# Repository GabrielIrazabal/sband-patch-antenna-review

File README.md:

# S-band patch antenna for a 1U CubeSat

A right-hand circularly polarized patch antenna for a 2.4 GHz downlink. This repo holds the two cut-corner designs, the three size versions planned for the first order, and the dual-feed designs as a supplement. Each one has its KiCad board, its Gerbers and its Ansys HFSS results.

**Status: simulation only. Nothing has been built or measured yet.**

Author: Gabriel Irazabal

## Contents

1. [Requirements](#1-requirements)
2. [How everything was simulated](#2-how-everything-was-simulated)
3. [Cut corner, 1.5 mm](#3-cut-corner-15-mm)
4. [Cut corner, 3 mm (stacked)](#4-cut-corner-3-mm-stacked)
5. [Manufacturing tolerance and the proposed first order](#5-manufacturing-tolerance-and-the-proposed-first-order)
6. [Supplementary: dual feed](#6-supplementary-dual-feed)
7. [How to check this work](#7-how-to-check-this-work)
8. [What has not been verified](#8-what-has-not-been-verified)

## 1. Requirements

| Requirement | Target |
| --- | --- |
| Frequency | 2.4 GHz band |
| Signal bandwidth | 20 MHz or less |
| Gain | 6.5 dBi or more (ideally 7 or more) |
| Beamwidth | half-power beamwidth 60° or wider |
| Polarization | right-hand circular |
| Impedance | 50 Ω |
| Power handling | 3 W or more |
| Environment | −40 to +85 °C |
| Direction | transmit and receive |
| Match bandwidth | return loss 10 dB or more across the full 20 MHz channel |
| Connector | SMA |

The designs are centred on 2.425 GHz, with the channel taken as 2.415 to 2.435 GHz.

## 2. How everything was simulated

| Item | Value |
| --- | --- |
| Tool | Ansys HFSS (Electronics Desktop Student 2025 R2) |
| Board material | JLCPCB PTFE, ZYF255DA: Dk 2.55, loss tangent 0.0018 |
| Board | 60 × 60 mm, 1.524 mm thick, 35 µm copper |
| Mounting | board flat on a 100 × 100 mm metal face, which stands in for the satellite panel |
| Feed | 0.5 mm pin through the board, 50 Ω lumped port |
| Mesh | refined to about 40,000 tetrahedra |
| Far field | RHCP and LHCP gain and axial ratio straight ahead, and gain against angle at 2.425 GHz |

In the plots, match is shown as S11. S11 is return loss with a minus sign, so "S11 of −10 dB or lower" is the same as "return loss of 10 dB or more".

## 3. Cut corner, 1.5 mm

One board. A square patch with two opposite corners clipped, fed by one pin. The clipped corners are what make it circularly polarized.

Folder: [`1_cut_corner_1.5mm`](1_cut_corner_1.5mm)

| Front | Back |
| --- | --- |
|  |  |

### Dimensions

| Item | Value |
| --- | --- |
| Board | 60 × 60 × 1.524 mm |
| Patch | 37.52 mm square, centred |
| Clipped corners | top-left and bottom-right (seen from the front), 3.50 mm along each edge |
| Feed | plated via, 0.5 mm hole, 7.00 mm to the right of the patch centre |
| Ground | whole back of the board |
| Connector | surface-mount SMA on the back (Würth 60312102114405), centre pad on the feed via |
| Solder mask | none on the front |
| Mounting holes | four M3, 4 mm in from each edge |

### Ansys HFSS results

| Requirement | Result | Meets it |
| --- | --- | --- |
| Frequency: 2.4 GHz band | best polarization at 2.425 GHz | yes |
| Signal bandwidth 20 MHz | return loss above 10 dB from 2.400 to 2.466 GHz (66 MHz) | yes |
| Gain 6.5 dBi or more | 7.08 to 7.24 dBic across the channel | yes |
| Beamwidth 60° or wider | 72° and 73° in the two cuts | yes |
| Right-hand circular | RHCP is 32 dB above LHCP at 2.425 GHz | yes |
| 50 Ω | best match −31.8 dB at 2.4455 GHz | yes |
| Return loss 10 dB over the channel | worst point in the channel 15.5 dB | yes |

Other figures: directivity 7.97 dBi, radiation efficiency 87 %.

**The known weak point is polarization at the channel edges.** The axial ratio is 0.43 dB at the centre and 4.14 dB at the edges, and it stays under 3 dB over 16 MHz. An axial ratio of 4.14 dB costs about 0.23 dB of signal to a perfectly circular ground antenna. The gain figures above already include that.

| Match | Axial ratio |
| --- | --- |
|  |  |

| Gain | Pattern |
| --- | --- |
|  |  |

### Files

| What | Where |
| --- | --- |
| KiCad project | [`1_cut_corner_1.5mm/kicad`](1_cut_corner_1.5mm/kicad) |
| Gerbers for JLCPCB | [`1_cut_corner_1.5mm/gerbers/Cutcorner_antenna.zip`](1_cut_corner_1.5mm/gerbers/Cutcorner_antenna.zip) |
| Ansys project and raw results | [`1_cut_corner_1.5mm/ansys`](1_cut_corner_1.5mm/ansys) |

## 4. Cut corner, 3 mm (stacked)

Folder: [`2_cut_corner_3mm_stacked`](2_cut_corner_3mm_stacked)

| TOP board, front | BOTTOM board, back |
| --- | --- |
|  |  |

### Dimensions

| Item | Value |
| --- | --- |
| Boards | two, each 60 × 60 × 1.524 mm, giving 3.05 mm of PTFE between patch and ground |
| Patch (on the TOP board) | 37.10 mm square, centred |
| Clipped corners | top-left and bottom-right, 5.55 mm along each edge |
| Feed | 0.6 mm hole through both boards, 8.00 mm to the right of the patch centre and 2.18 mm up |
| Ground (on the BOTTOM board) | whole back |
| Connector | the same SMA, on the back of the BOTTOM board |
| Copper on the two glued faces | none |

The feed sits 2.18 mm off the centre line on purpose. A pin through 3 mm of board adds inductance, and the sideways offset cancels it.

### How it goes together

1. Glue the TOP board onto the BOTTOM board with a thin, even layer of adhesive, using the four M3 holes to line them up. There must be no air between them.
2. Solder the SMA to the back of the BOTTOM board.
3. Pass a 0.5 mm wire through the feed hole in both boards. Solder it to the SMA centre pad at the back and to the patch at the front, and trim it flush.

The wire is needed because the plating inside each board's hole does not connect across the glue layer.

### Ansys HFSS results

| Requirement | Result | Meets it |
| --- | --- | --- |
| Frequency: 2.4 GHz band | best polarization at 2.425 GHz | yes |
| Signal bandwidth 20 MHz | return loss above 10 dB from 2.356 to 2.487 GHz (131 MHz) | yes |
| Gain 6.5 dBi or more | 7.61 to 7.67 dBic across the channel | yes |
| Beamwidth 60° or wider | 73° in both cuts | yes |
| Right-hand circular | RHCP is 33 dB above LHCP at 2.425 GHz | yes |
| 50 Ω | best match −38.6 dB at 2.394 GHz | yes |
| Return loss 10 dB over the channel | worst point in the channel 19.1 dB | yes |

Other figures: directivity 7.96 dBi, radiation efficiency 95 %. The axial ratio is 0.38 dB at the centre and 2.17 dB at the channel edges, and stays under 3 dB over 32 MHz.

| Match | Axial ratio |
| --- | --- |
|  |  |

| Gain | Pattern |
| --- | --- |
|  |  |

### Thin against thick

| | Cut corner, 1.5 mm | Cut corner, 3 mm |
| --- | --- | --- |
| RHCP gain in the channel | 7.08 to 7.24 dBic | 7.61 to 7.67 dBic |
| Worst return loss in the channel | 15.5 dB | 19.1 dB |
| Match bandwidth | 66 MHz | 131 MHz |
| Axial ratio at the channel edges | 4.14 dB | 2.17 dB |
| Bandwidth with axial ratio under 3 dB | 16 MHz | 32 MHz |
| Efficiency | 87 % | 95 % |
| Build | one board | two boards, a glue joint and a feed wire |

**The weak point of the 3 mm version is the glue joint.** In simulation, a 0.05 mm film of air between the boards raises the worst axial ratio in the channel from 2.2 to 6.5 dB.

### Files

| What | Where |
| --- | --- |
| KiCad projects, TOP and BOTTOM | [`2_cut_corner_3mm_stacked/kicad`](2_cut_corner_3mm_stacked/kicad) |
| Gerbers for JLCPCB | [`2_cut_corner_3mm_stacked/gerbers`](2_cut_corner_3mm_stacked/gerbers) |
| Ansys project and raw results | [`2_cut_corner_3mm_stacked/ansys`](2_cut_corner_3mm_stacked/ansys) |

## 5. Manufacturing tolerance and the proposed first order

**Proposal: order the 1.5 mm cut corner in three sizes (the design size, 0.3 mm smaller and 0.3 mm larger), measure all of them, and fly the one closest to 2.425 GHz.** This section explains the problem that makes this necessary.

Folder: [`3_three_sizes`](3_three_sizes) (the design size is in [`1_cut_corner_1.5mm`](1_cut_corner_1.5mm))

### The problem

A patch antenna's frequency is set by the patch size and the board it sits on, and a factory cannot make either exactly as drawn. For JLCPCB's PTFE (ZYF255DA, 1.524 mm) the expected errors are:

| What varies | By how much | Frequency shift |
| --- | --- | --- |
| Dk of the PTFE | 2.55 ± 0.04 (laminate datasheet) | about ±18 MHz |
| Board thickness | ±10 % (JLCPCB) | about ±9 MHz (+10 thin, −7.5 thick) |
| Etched patch size | about ±0.05 mm | about ±3 MHz |
| **All together** | | **about ±20 to ±23 MHz** |

The total is the root-sum-square of the three, since they are independent. That is as wide as the 20 MHz channel itself. The Dk figure comes from HFSS runs of this board with Dk set to 2.52 and 2.58, and the patch-size figure from the three sizes below. The thickness figure is from a separate check in a second solver (openEMS) at 1.37 and 1.68 mm.

Sources: [ZYF255DA datasheet (hosted by JLCPCB)](https://rs.jlcpcb.com/static/file/ptfe-teflon-datasheet.pdf), [JLCPCB PCB capabilities](https://jlcpcb.com/capabilities/pcb-capabilities).

### What an off-frequency board does

The table reads the design-size HFSS curves as if the whole antenna had moved up or down in frequency, and reports the worst point inside the 2.415 to 2.435 GHz channel.

| Board lands | Worst axial ratio | Lowest RHCP gain | Worst return loss | Meets gain 6.5 and return loss 10? |
| --- | --- | --- | --- | --- |
| On target | 4.1 dB | 7.08 dBic | 15.5 dB | yes |
| 10 MHz high | 7.0 dB | 6.47 dBic | 12.3 dB | gain just under |
| 10 MHz low | 7.6 dB | 6.72 dBic | 15.5 dB | yes |
| 20 MHz high | 10.4 dB | 5.49 dBic | 8.2 dB | no |
| 20 MHz low | 10.9 dB | 6.17 dBic | 16.6 dB | gain no |

The gain column is realized gain, so it already includes the polarization and mismatch losses. Polarization degrades first: the cut corner keeps its axial ratio under 3 dB over only 16 MHz. The 20 MHz rows use the end of the HFSS sweep (2.395 GHz), so they are approximate.

### Temperature

The Dk of the PTFE changes by −115 ppm/°C (datasheet), and the copper grows by about 15.5 ppm/°C, which partly cancels it. In HFSS the 1.5 mm cut corner moves −5 MHz at −40 °C and +6 MHz at +85 °C, and still meets the requirements at both:

| 1.5 mm cut corner | Best match moves | Lowest gain | Worst return loss | Worst axial ratio |
| --- | --- | --- | --- | --- |
| −40 °C | −5.0 MHz | 6.87 dBic | 15.1 dB | 6.1 dB |
| 20 °C (nominal) | 0 | 7.08 dBic | 15.5 dB | 4.1 dB |
| +85 °C | +6.0 MHz | 6.73 dBic | 13.3 dB | 5.9 dB |

This drift comes on top of the manufacturing error, and it affects every board the same way, so choosing a size cannot remove it. It is about ±6 MHz, so a board that lands within about ±10 MHz at room temperature still has some margin. The 1.5 mm dual feed fails this same check (section 6).

### Options considered

| Option | Frequency error | Notes |
| --- | --- | --- |
| **JLCPCB PTFE, three sizes** (proposed) | about ±20 MHz, covered by the three sizes | $175 per size (5 boards), about $525 for all three. Designed and simulated. |
| JLCPCB PTFE, one size | about ±20 MHz | A board 20 MHz off misses the gain requirement (table above). |
| Rogers RO4350B or RO4003C | about ±17 MHz | Dk 3.48 / 3.38 ± 0.05. Tolerance barely better, and RO4350B simulated at 5.6 to 6.3 dBic, below the 6.5 requirement. |
| Rogers RT/duroid 5880 (or Taconic TLY-5) | about ±12 MHz (estimate) | Dk 2.20 ± 0.02, 1.575 mm ± 0.076 mm. Roughly halves the error. Not designed or simulated yet (patch about 40 mm). Not offered by JLCPCB. PCBWay lists it, but only as a manual quote for non-stocked material. |

Sources: [RT/duroid 5880 datasheet (Rogers)](https://www.rogerscorp.com/-/media/project/rogerscorp/documents/advanced-electronics-solutions/english/data-sheets/rt-duroid-5870---5880-data-sheet.pdf), [PCBWay material list](https://www.pcbway.com/pcb_prototype/PCB_material_classification.html).

### What changed between the three sizes

Only the side of the patch. The corner cuts, the feed position, the board and everything else are identical. A smaller patch resonates higher and a larger one lower.

| Version | Patch side | Best polarization at | Best match at | Shift from the design size |
| --- | --- | --- | --- | --- |
| Smaller | 37.22 mm | 2.4425 GHz | 2.4630 GHz | +17.5 MHz |
| Design size | 37.52 mm | 2.4250 GHz | 2.4455 GHz | 0 |
| Larger | 37.82 mm | 2.4050 GHz | 2.4280 GHz | −17.5 to −20 MHz |

So the three are about 19 MHz apart, or about 62 MHz per millimetre of patch side. The far-field sweep is in 2.5 MHz steps, which is why the two shifts are not exactly equal.

### How they are used

All three are made in the same batch, so they share the same material and thickness errors. Each is measured on a network analyzer, and the one that lands closest to 2.425 GHz is the one that flies. If the factory makes everything about 20 MHz low, that is the smaller one; if about 20 MHz high, the larger one.

Because the sizes are 19 MHz apart, the best of the three should land within about ±10 MHz of 2.425 GHz for any factory error up to about ±30 MHz. From the table above, a board 10 MHz off still gives about 6.5 to 6.7 dBic. A spare from the same batch is the backup for the flight board.

### Files

| What | Where |
| --- | --- |
| KiCad projects | [`3_three_sizes/kicad`](3_three_sizes/kicad) |
| Gerbers for JLCPCB | [`3_three_sizes/gerbers`](3_three_sizes/gerbers) |
| Ansys projects and raw results | [`3_three_sizes/ansys`](3_three_sizes/ansys) |

## 6. Supplementary: dual feed

The other way to make a patch circularly polarized. A plain square patch gets two feed pins, one on each axis, driven a quarter cycle apart by an external 90° coupler. It is not the plan for this satellite, because the radio board has one S-band connector and no coupler, but it was designed and simulated as the alternative.

Folder: [`supplementary_dual_feed`](supplementary_dual_feed)

| Front | Back |
| --- | --- |
|  |  |

### Dimensions

| | Dual feed, 1.5 mm | Dual feed, 3 mm (stacked) |
| --- | --- | --- |
| Patch | 37.28 mm square | 36.39 mm square |
| Clipped corners | none | none |
| Feeds | 5.80 mm right of centre (J1) and 5.80 mm above centre (J2) | 6.70 mm right of centre (J1) and 6.70 mm above centre (J2) |
| Connectors | two SMAs | two SMAs |
| Build | one board | TOP and BOTTOM boards glued, as in section 4 |

It is right-hand circular when J2 lags J1 by 90°.

### Ansys HFSS results

| | Dual feed, 1.5 mm | Dual feed, 3 mm |
| --- | --- | --- |
| RHCP gain in the channel, at the patch | 7.16 to 7.36 dBic | 7.67 to 7.72 dBic |
| RHCP gain after a typical coupler | 6.75 to 6.96 dBic | 7.26 to 7.32 dBic |
| Worst return loss in the channel | 13.6 dB | 16.4 dB |
| Match bandwidth | 32 MHz | 63 MHz |
| Axial ratio, perfect coupler | 0.11 dB | 0.28 dB |
| Axial ratio, typical coupler | 0.79 dB | 0.94 dB |
| Isolation between the two feeds | 46 dB | 36 dB |
| Half-power beamwidth | 72° and 73° | 73° |
| Radiation efficiency | 87 % | 95 % |

"Typical coupler" means one that is off by 0.5 dB and 3° and loses 0.4 dB. The coupler itself was not modelled.

### Temperature and manufacturing checks: the 1.5 mm dual feed does not hold

Both dual feeds were rerun in HFSS (24 and 25 November) with the effects that real boards add. For temperature, the Dk was scaled by the datasheet's −115 ppm/°C and the copper dimensions by 15.5 ppm/°C, from 20 °C. The whole board was held at one temperature.

| Dual feed, 1.5 mm | Best match moves | Lowest gain (after coupler) | Worst return loss | Requirements |
| --- | --- | --- | --- | --- |
| Nominal | 0 | 6.75 dBic | 13.6 dB | pass |
| Finest mesh | +1.0 MHz | 6.70 dBic | 12.8 dB | pass |
| With the SMA connector | −4.0 MHz | 6.58 dBic | 11.0 dB | pass |
| With solder mask on the top | −8.5 MHz | 6.38 dBic | 9.1 dB | **fail** |
| −40 °C | −6.5 MHz | 6.50 dBic | 9.9 dB | **fail** |
| +85 °C | +6.5 MHz | 6.43 dBic | 9.8 dB | **fail** |

**Its match window is only 32 MHz wide, and a ±6 MHz temperature drift is enough to take the channel edge below 10 dB return loss.** It fails the match requirement at both temperature extremes and the gain requirement at +85 °C. The manufacturing tolerances in section 5 (about ±20 MHz) are three times larger than that drift, so this design has no margin left for them. The second solver (openEMS) already put it at 6.49 dBic at nominal.

| Dual feed, 3 mm | Best match moves | Lowest gain (after coupler) | Worst return loss | Requirements |
| --- | --- | --- | --- | --- |
| Nominal | 0 | 7.26 dBic | 16.4 dB | pass |
| −40 °C / +85 °C | −5.5 / +6.0 MHz | 7.18 / 7.21 dBic | 13.9 / 15.8 dB | pass |
| SMA and glue-joint layer, as drawn | −15.0 MHz | 6.99 dBic | 10.8 dB | pass, narrowly |
| The same plus solder mask on the top | −24.0 MHz | 6.83 dBic | 9.0 dB | **fail** |

The 3 mm dual feed survives temperature, but the SMA, the glue joint and any top mask all pull it lower in frequency, and the shifts add up. As drawn it keeps only 0.8 dB of return loss in hand, before manufacturing tolerance is counted.

For comparison, both cut corners pass all of these checks on gain and return loss (section 5 has the 1.5 mm temperature figures).

### Compared with the cut corner

| | Cut corner | Dual feed |
| --- | --- | --- |
| Polarization | good at the centre, weaker at the channel edges | good across the whole channel |
| Extra parts | none | a 90° coupler, a load, a second cable and a second connector |
| Gain | higher | about 0.3 to 0.4 dB lower, because of the coupler |
| Match bandwidth | wider | half as wide |
| −40 °C and +85 °C (HFSS) | holds at 1.5 mm and 3 mm | fails at 1.5 mm, holds at 3 mm |

### Files

| What | 1.5 mm | 3 mm |
| --- | --- | --- |
| KiCad | [`kicad`](supplementary_dual_feed/1.5mm/kicad) | [`kicad`](supplementary_dual_feed/3mm_stacked/kicad) |
| Gerbers | [`gerbers`](supplementary_dual_feed/1.5mm/gerbers) | [`gerbers`](supplementary_dual_feed/3mm_stacked/gerbers) |
| Ansys project and raw results | [`ansys`](supplementary_dual_feed/1.5mm/ansys) | [`ansys`](supplementary_dual_feed/3mm_stacked/ansys) |
| Plots | [`plots`](supplementary_dual_feed/1.5mm/plots) | [`plots`](supplementary_dual_feed/3mm_stacked/plots) |

## 7. How to check this work

Each `ansys` folder holds:

| File | What it is |
| --- | --- |
| `*.aedt` | the Ansys Electronics Desktop project. Open it to see the model, materials and setup, and re-solve it |
| `summary.txt` | the headline numbers from that run |
| `sparams.csv` | S11 against frequency |
| `farfield_boresight.csv` | RHCP and LHCP gain and axial ratio against frequency, straight ahead |
| `pattern_f0.csv` | gain against angle at 2.425 GHz |
| `convergence.txt` | the mesh refinement passes |

`summary.txt` flags the axial ratio against a limit of 3 dB. That is a common target and is not one of the requirements in section 1.

Suggested checks:

1. **Dimensions.** Open a KiCad board and measure the patch, the corner cuts and the feed position against the tables above. Then open the matching `.aedt` and confirm the model has the same numbers.
2. **Materials.** In the `.aedt`, the substrate should be Dk 2.55, loss tangent 0.0018, 1.524 mm (3.048 mm for the stacked designs).
3. **Polarization hand.** The clipped corners are top-left and bottom-right seen from the front, with the feed on the right. That combination gives right-hand circular polarization. `summary.txt` reports RHCP well above LHCP.
4. **Results.** Compare the tables in this README with `summary.txt`, or re-plot from the CSV files.
5. **Gerbers.** Open a zip in any Gerber viewer and confirm it shows the same patch as the KiCad board.

## 8. What has not been verified

- **Nothing has been built or measured.** A network analyzer measurement of the first boards is the real test.
- **Power handling (3 W)** has not been simulated or tested.
- **Temperature (−40 to +85 °C)** has only been simulated as a steady state, with the whole board at one temperature and the datasheet's Dk drift (sections 5 and 6). It has not been tested.
- **The real mounting.** Every result assumes a clean 100 mm metal face behind the board, with nothing else near the patch.
- **The SMA connector** is not in these models. In a separate run it moved the 1.5 mm cut corner about 3 MHz lower.
- **The coupler** for the dual feed is assumed, not modelled.
- **The carrier frequency** is taken as 2.425 GHz.

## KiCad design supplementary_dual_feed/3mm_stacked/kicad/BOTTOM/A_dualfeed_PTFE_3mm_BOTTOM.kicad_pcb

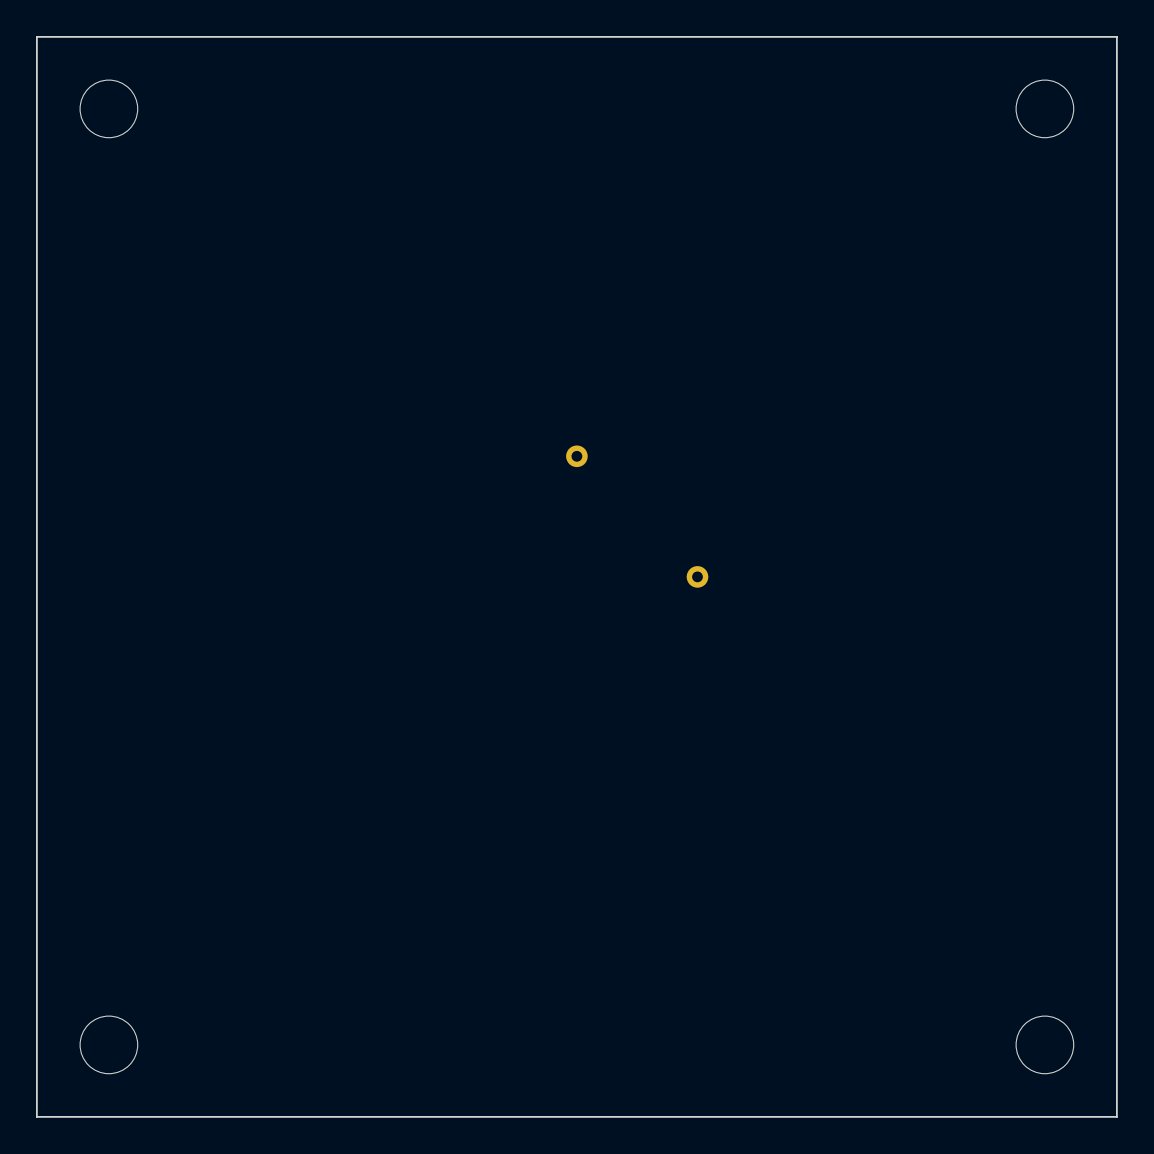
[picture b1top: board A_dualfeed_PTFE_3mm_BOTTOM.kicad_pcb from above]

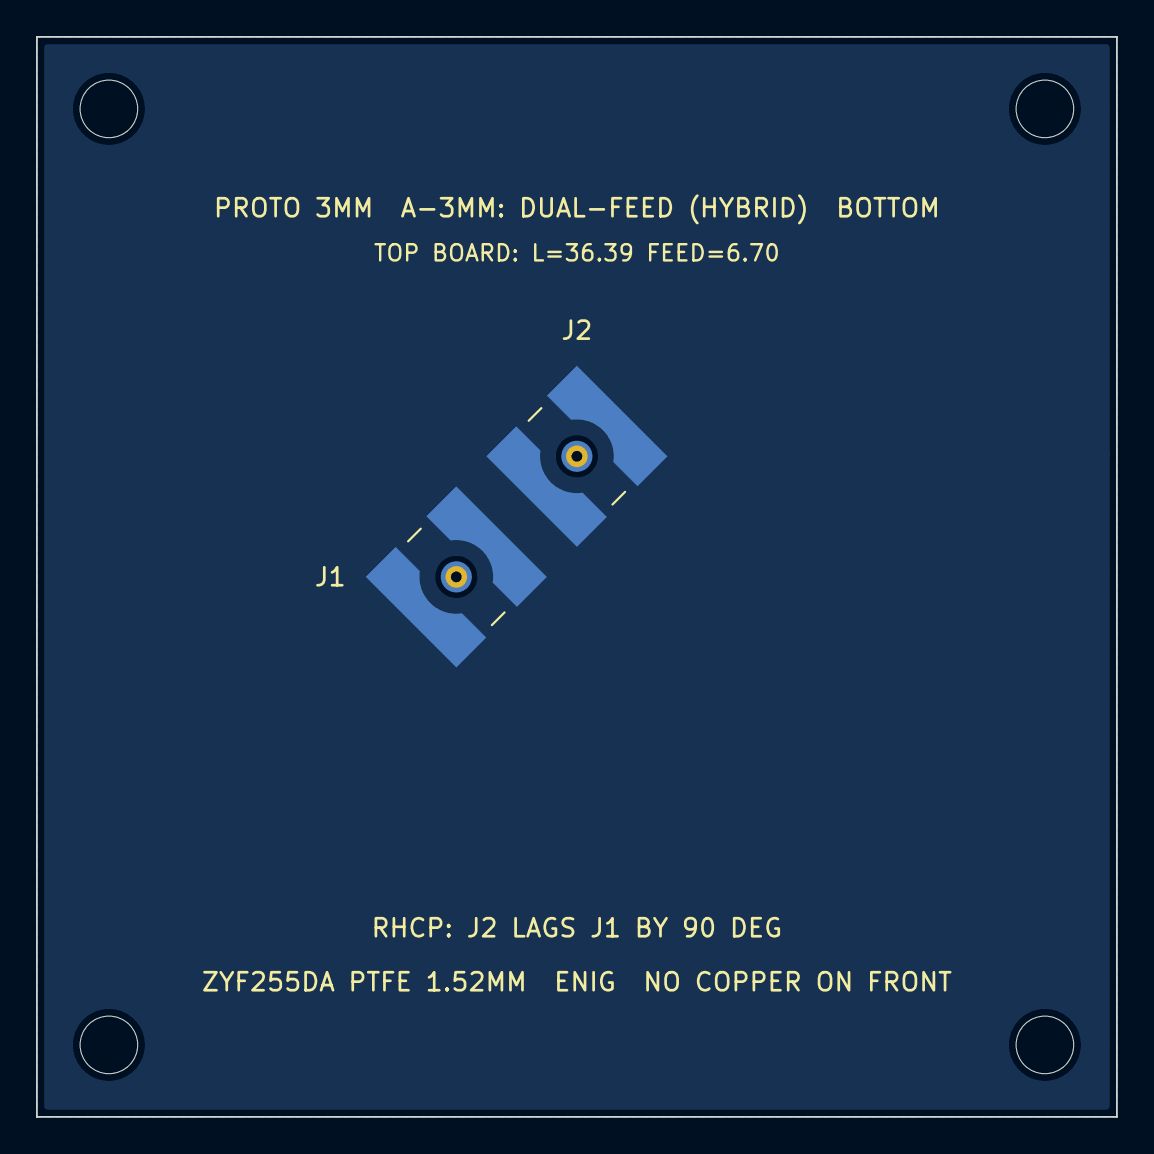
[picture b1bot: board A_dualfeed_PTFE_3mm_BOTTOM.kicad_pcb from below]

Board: 2 copper layers, 60.0 x 60.0 mm, 8 parts (2 on the bottom side), 3 nets, no tracks yet.

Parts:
H1, H2, H3, H4: MountingHole_3.2mm_M3
J1, J2: Wurth WR-SMA 60312102114405; SMA_Wurth_60312102114405_Vertical
P1, P2: (no value)

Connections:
FEED1: J1.1, P1.1
FEED2: J2.1, P2.1
GND: J1.2, J2.2
